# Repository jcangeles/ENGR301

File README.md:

# ENGR301  

SFSU - ENGR 301 Microelectronics Lab  

Final Project - Low Noise Headphone Amplifier  

See final report for documentation.

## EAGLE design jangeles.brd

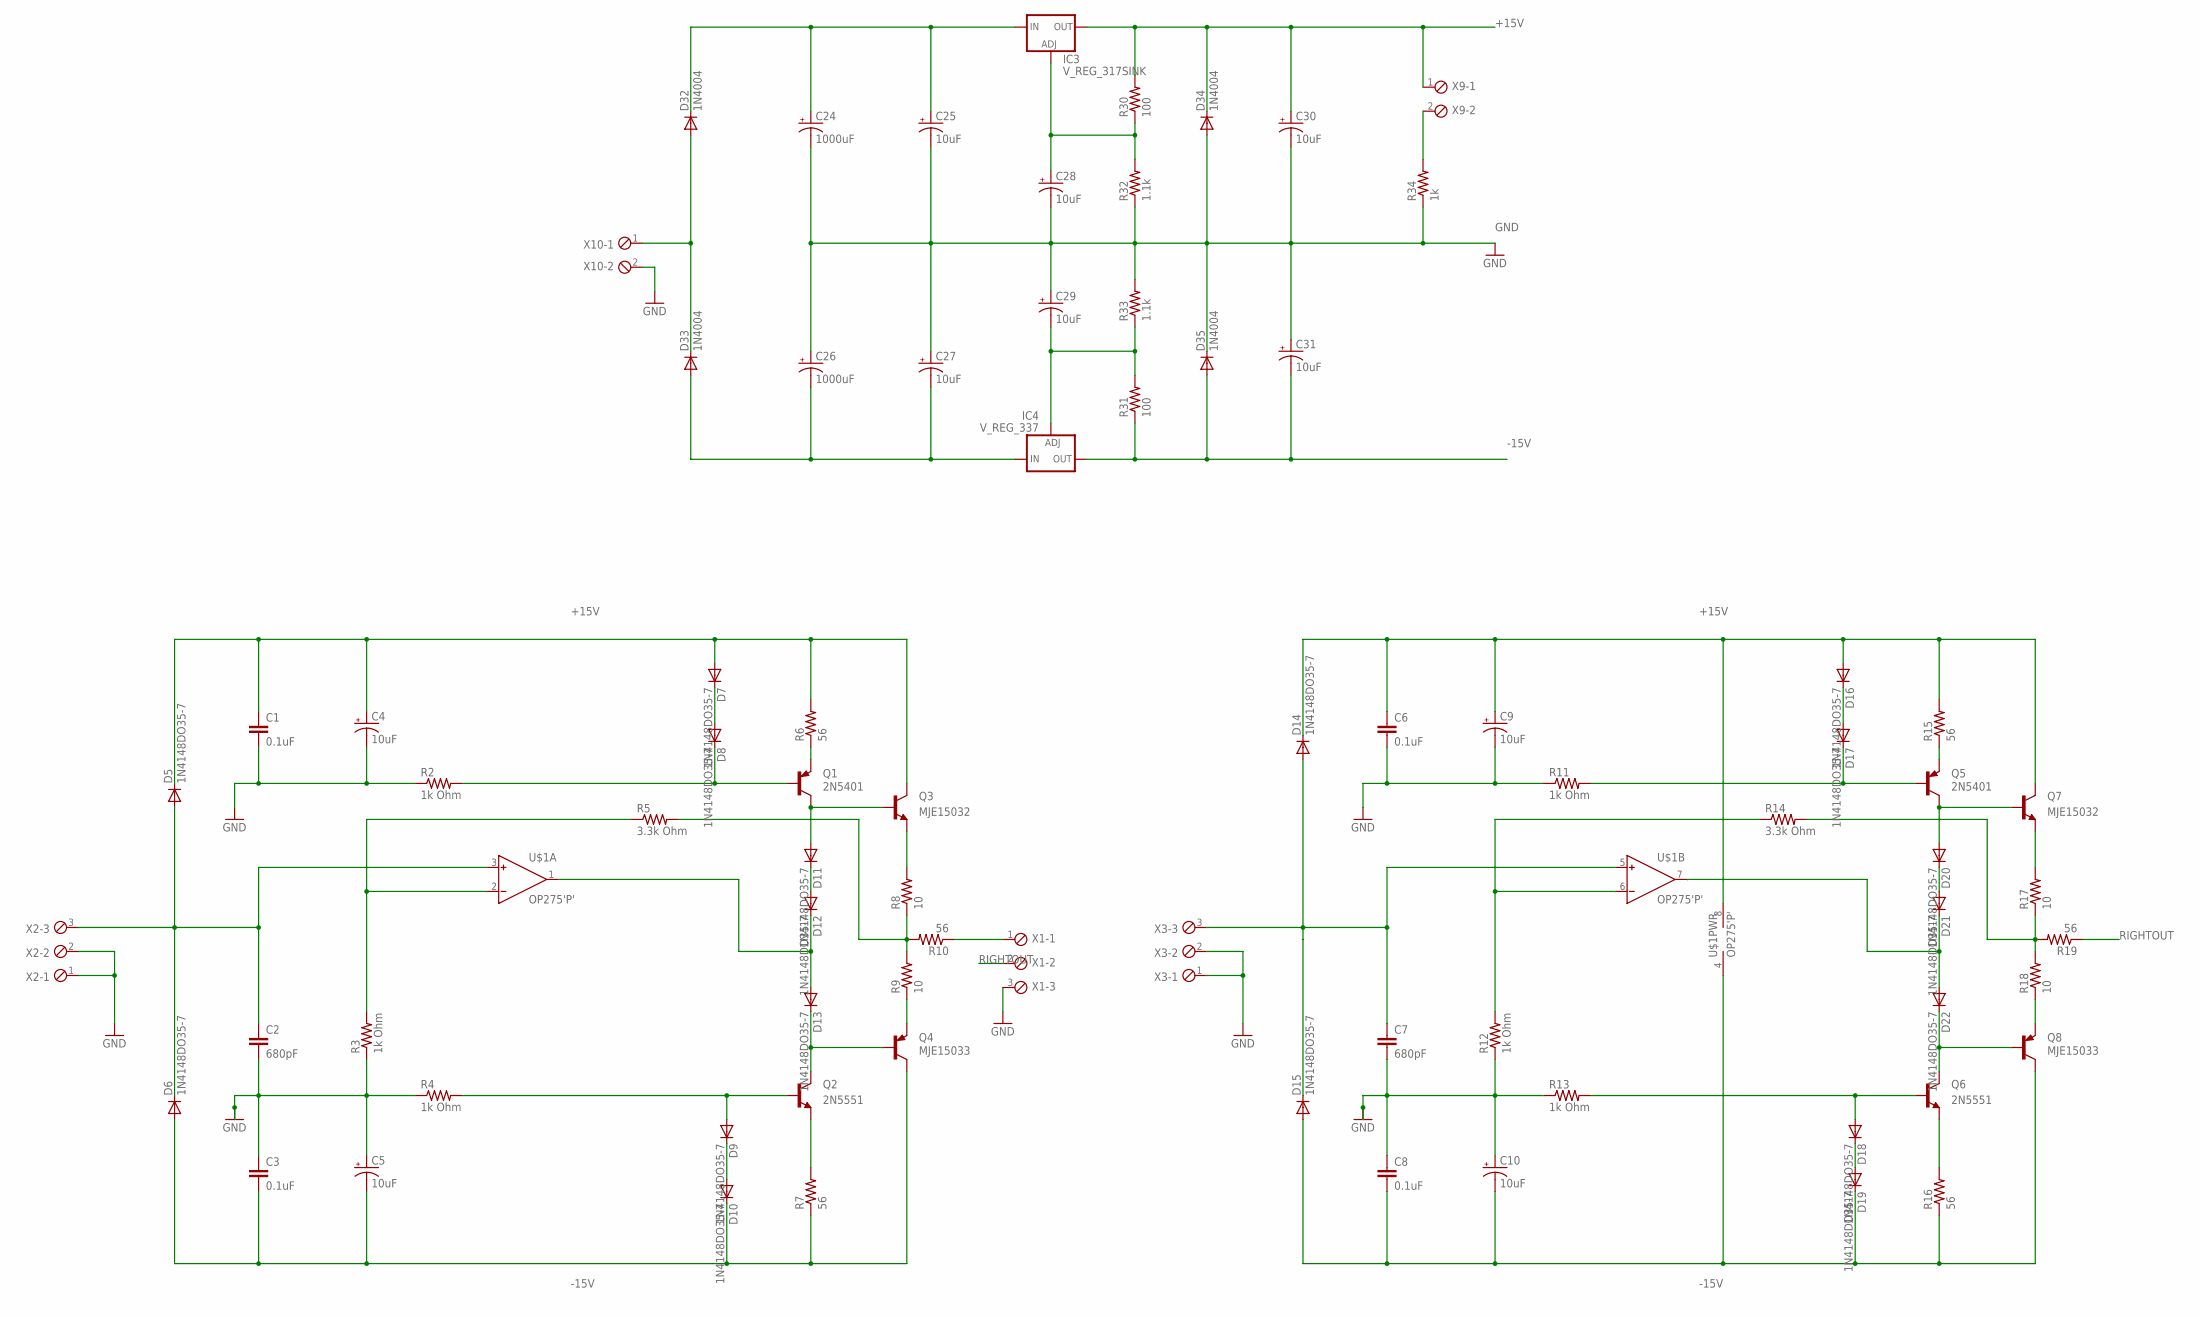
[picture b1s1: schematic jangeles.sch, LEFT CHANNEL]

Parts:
C1, C3, C6, C8: 0.1uF; C025-024X044
C2, C7: 680pF; C025-024X044
C4, C5, C9, C10, C25, C27, C28, C29, C30, C31: 10uF; E2-5
C24, C26: 1000uF; E5-10,5
D5, D6, D7, D8, D9, D10, D11, D12, D13, D14, D15, D16, D17, D18, D19, D20, D21, D22: 1N4148DO35-7; DO35-7
D32, D33, D34, D35: 1N4004; DO41-10
IC3: V_REG_317SINK; TO220-ADJ
IC4: V_REG_337; TO220-ADJ-NEG
Q1, Q5: 2N5401
Q2, Q6: 2N5551
Q3, Q7: MJE15032; TO220V
Q4, Q8: MJE15033; TO220V
R2, R3, R4, R11, R12, R13: 1k Ohm; 0204/5
R5, R14: 3.3k Ohm; 0204/5
R6, R7, R10, R15, R16, R19: 56; 0204/5
R8, R9, R17, R18: 10; 0204/5
R30, R31: 100; 0309/10
R32, R33: 1.1k; 0204/5
R34: 1k; 0204/5
U$1: OP275'P'; DIL08
X1, X2, X3: MPT3; 3POL254
X9, X10: MPT2; 2POL254

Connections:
+15V: C1.1, C4.+, C6.1, C9.+, C30.+, D5.C, D7.A, D14.C, D16.A, D34.C, IC3.OUT, Q3.2 (C), Q7.2 (C), R6.2, R15.2, R30.2, U$1.8 (V+), X9.1
-15V: C3.2, C5.-, C8.2, C10.-, C31.-, D6.A, D10.C, D15.A, D19.C, D35.A, IC4.OUT, Q4.2 (C), Q8.2 (C), R7.1, R16.1, R31.1, U$1.4 (V-)
GND: C1.2, C2.2, C3.1, C4.-, C5.+, C6.2, C7.2, C8.1, C9.-, C10.+, C24.-, C25.-, C26.+, C27.+, C28.-, C29.+, C30.-, C31.+, D34.A, D35.C, R2.1, R3.1, R4.1, R11.1, R12.1, R13.1, R32.1, R33.2, R34.1, X1.3, X2.1, X2.2, X3.1, X3.2, X10.2
unnamed: D7.C, D8.A
unnamed: D9.C, D10.A
unnamed: Q2.E, R7.2
unnamed: D9.A, Q2.B, R4.2
unnamed: R3.2, R5.1, U$1.2 (IN-)
unnamed: D18.C, D19.A
unnamed: Q3.3 (E), R8.2
unnamed: R5.2, R8.1, R9.2, R10.2
unnamed: Q4.3 (E), R9.1
unnamed: D13.C, Q2.C, Q4.1 (B)
unnamed: D12.C, D13.A, U$1.1 (OUT)
unnamed: D11.C, D12.A
unnamed: D11.A, Q1.C, Q3.1 (B)
unnamed: Q1.E, R6.1
unnamed: Q6.E, R16.2
unnamed: D18.A, Q6.B, R13.2
unnamed: D8.C, Q1.B, R2.2
unnamed: Q7.3 (E), R17.2
unnamed: R14.2, R17.1, R18.2, R19.2
unnamed: Q8.3 (E), R18.1
unnamed: D22.C, Q6.C, Q8.1 (B)
unnamed: D21.C, D22.A, U$1.7 (OUT)
unnamed: D20.C, D21.A
unnamed: D20.A, Q5.C, Q7.1 (B)
unnamed: Q5.E, R15.1
unnamed: D17.C, Q5.B, R11.2
unnamed: R12.2, R14.1, U$1.6 (IN-)
unnamed: D16.C, D17.A
unnamed: R10.1, X1.1
unnamed: D32.A, D33.C, X10.1
unnamed: C26.-, C27.-, D33.A, IC4.IN
unnamed: C24.+, C25.+, D32.C, IC3.IN
unnamed: C29.-, IC4.ADJ, R31.2, R33.1
unnamed: C28.+, IC3.ADJ, R30.1, R32.2
unnamed: R34.2, X9.2
R2: C7.1, D14.A, D15.C, U$1.5 (IN+), X3.3
R5: C2.1, D5.A, D6.C, U$1.3 (IN+), X2.3
RIGHTOUT: R19.1, X1.2

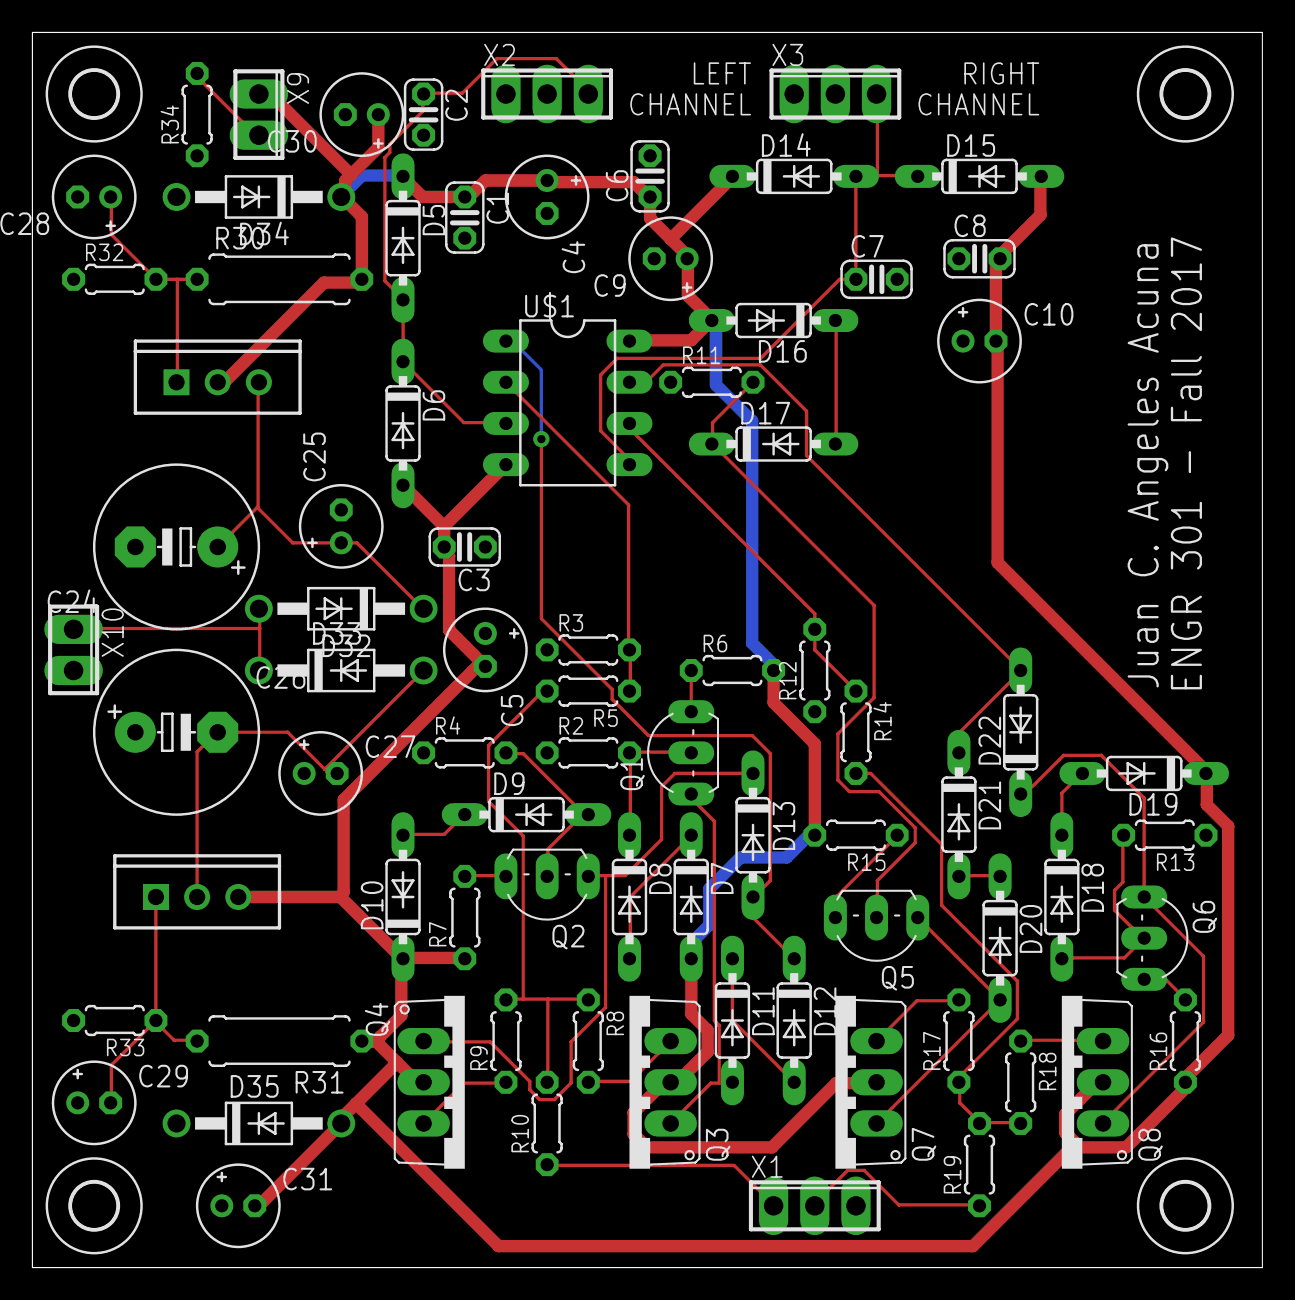
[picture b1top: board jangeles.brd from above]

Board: 2 copper layers, 75.9 x 76.2 mm, 83 parts (0 on the bottom side), 41 nets.

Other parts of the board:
U$2, U$3, U$4, U$5: 2,8

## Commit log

2019-01-30 Schematic, board, and gerber files.
